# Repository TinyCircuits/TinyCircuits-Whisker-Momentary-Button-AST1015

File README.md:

# TinyCircuits Wireling Momentary Button
# AST1015 Rev1

The design files are located under design_files/ for the TinyCircuits AST1015 Rev 1 PCB. This is a Wireling board which features a tiny tactile switch used for sending High/Low signals.

Format is in Cadsoft Eagle format - Eagle version 6.2 was used for the original design.

For more infomation on this, check out the product page at TinyCircuits.com

# License:

Design by TinyCircuits.
All design files are released under the Creative Commons Attribution Share-Alike 3.0 License, see the following link for details: http://creativecommons.org/licenses/by-sa/3.0

All text above must be included in any redistribution or derived design

This project uses designs and concepts developed as part of the Arduino project and the LilyPad project.  The TinyCircuits design files themselves (schematics, PCB and libraries) are not directly derived from these works' design files and have been created new, however the concepts and basic architecture behind the TinyDuino and TinyLily products are derived and we thank the hard work of the organizations below for their contributions to open-source hardware:
  
Original Arduino Uno Design by Team Arduino

LilyPad Arduino Design by Leah Buechley and Sparkfun Electronics

Please support the open-source hardware community

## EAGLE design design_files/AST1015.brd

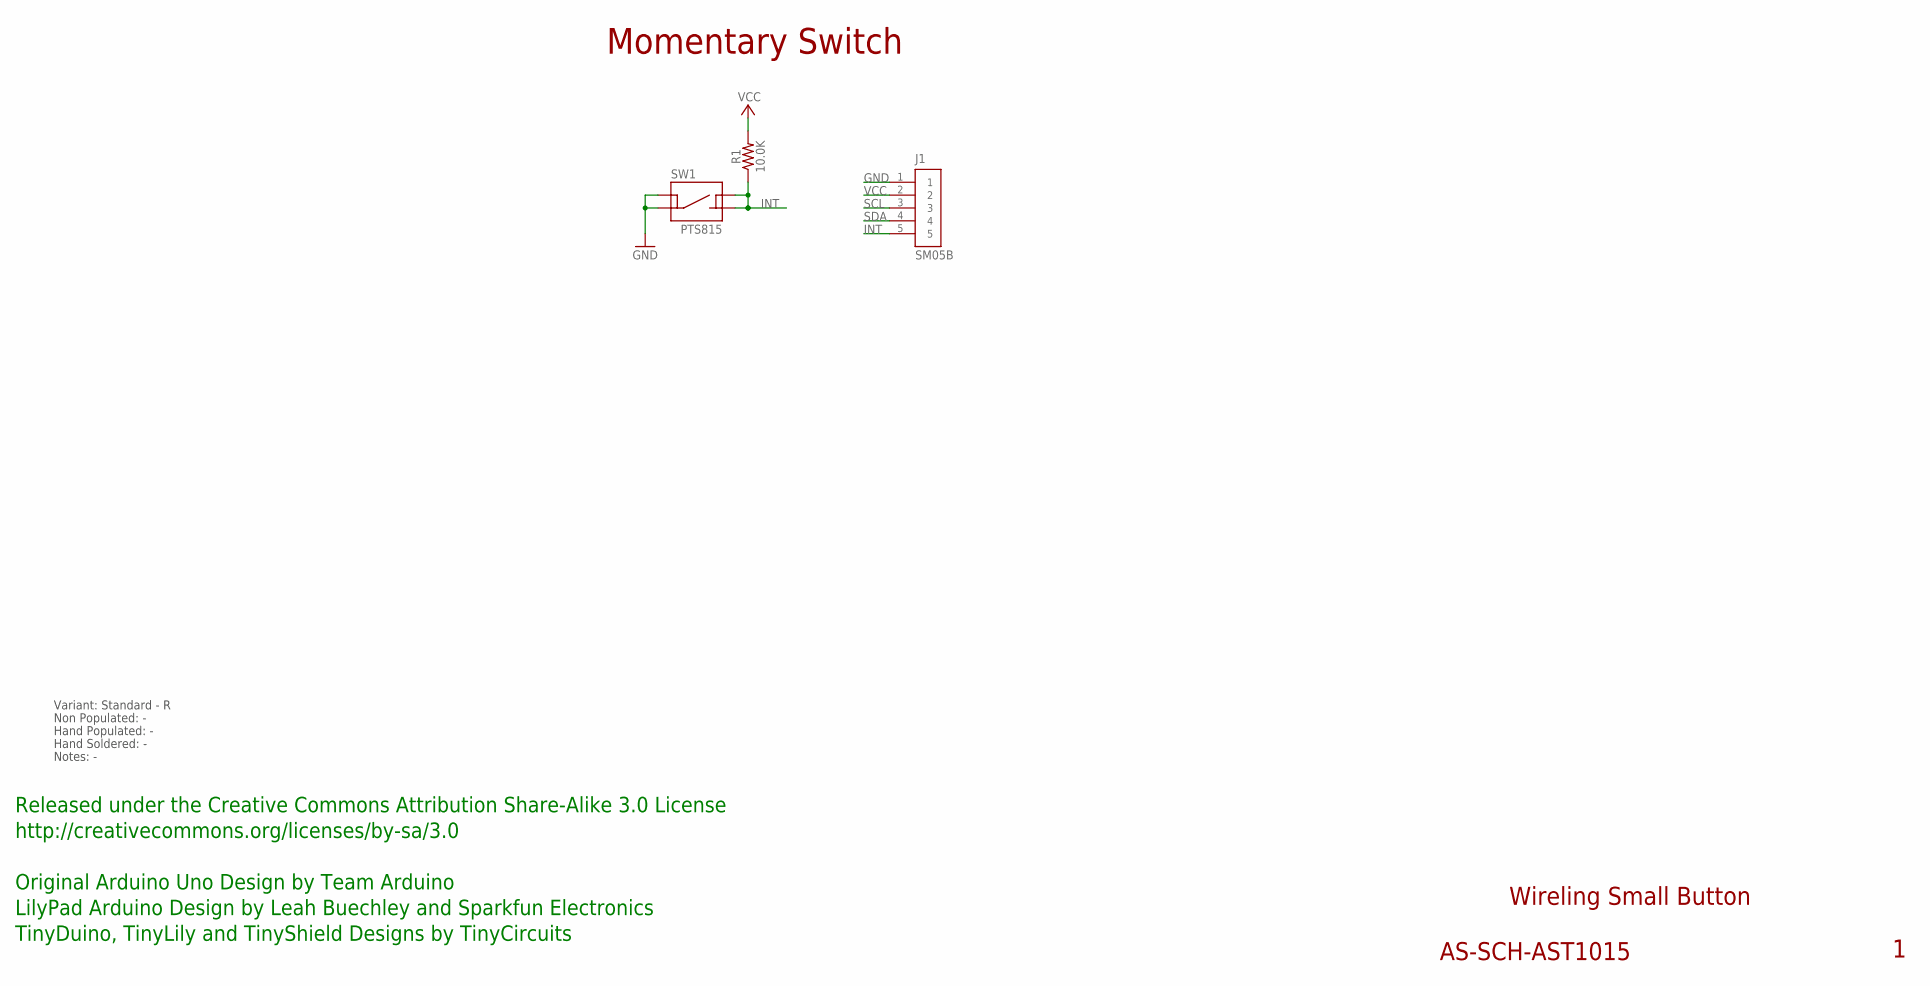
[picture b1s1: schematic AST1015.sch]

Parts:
J1: SM05B; JST_SH_5X1_EDGE
R1: 10.0K; 0402
SW1: PTS815

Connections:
GND: J1.1, SW1.1, SW1.2 (3)
INT: J1.5, R1.1, SW1.3 (2), SW1.4
SCL: J1.3
SDA: J1.4
VCC: J1.2, R1.2

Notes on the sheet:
Wireling Small Button
AS-SCH-AST1015
Momentary Switch
Released under the Creative Commons Attribution Share-Alike 3.0 License
http://creativecommons.org/licenses/by-sa/3.0
Original Arduino Uno Design by Team Arduino
TinyDuino, TinyLily and TinyShield Designs by TinyCircuits
LilyPad Arduino Design by Leah Buechley and Sparkfun Electronics
Non Populated: -
Hand Populated: -
Hand Soldered: -
Notes: -
Variant: Standard - R

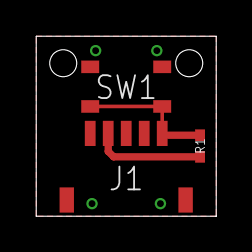
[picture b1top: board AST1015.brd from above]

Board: 2 copper layers, 10.0 x 10.0 mm, 4 parts (0 on the bottom side), 3 nets.

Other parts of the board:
U$1: DOCFIELD-TINYCIRCUITS-PCB

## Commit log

2019-07-30 updated to use Port 0
2019-07-30 cleaned up code
2019-08-05 added datasheet
2019-10-18 name change
2019-12-17 updated documentation
2020-02-04 mass image update
2020-08-14 Add CAD data
